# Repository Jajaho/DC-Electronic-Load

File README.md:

# DC-Electronic-Load
Digitally controlled dc electronic load.  

To cut costs, the core idea is to use multiple smaller low-cost MOSFETs in parallel instead of a single higher-power device.
Since the current through a semiconductor has a positive temperature coefficient this presents a novel engineering challenge. An unsuitable design could risk a thermal runaway event where a single transistor would handle increasingly larger currents until failure. To prevent such a catastrophic event a circuit to ensure equal current distribution is implemented.  

The instrument should feature constant current, voltage and power modes. Over-voltage and current protection is also desired.

This project was initially started in Eagle ECAD on 28.05.2019 but was never implemented.

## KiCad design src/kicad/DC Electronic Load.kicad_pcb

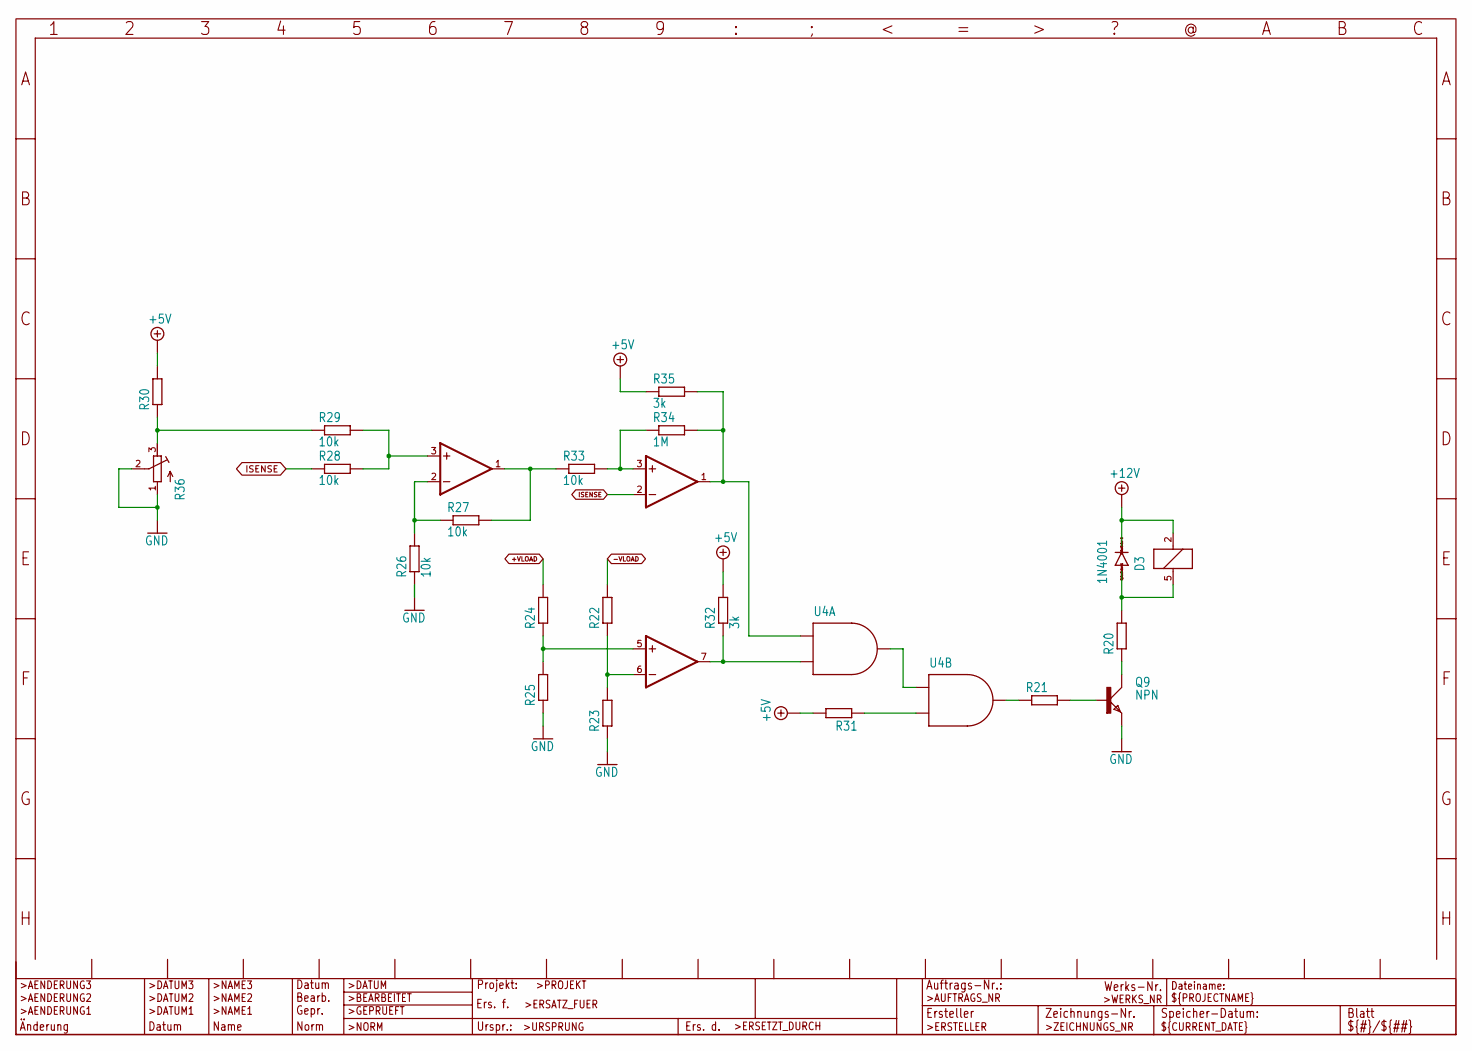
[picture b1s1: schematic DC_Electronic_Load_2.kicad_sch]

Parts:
D3: 1N4001; MELF-MLL41
IC1: LM393D; SO08
IC2: TL072D; SO08
K1: AZ8-FORM-C; AZ8
Q9: NPN; SOT23
R20, R21, R22, R23, R24, R25, R30, R31: R-EU_R1206; R1206
R26, R27, R28, R29, R33: 10k; R1206
R32, R35: 3k; R1206
R34: 1M; R1206
R36: R-TRIMM64W; RTRIM64W
U4: SN74AHC08; SOIC−14

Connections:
+5V: R30.2, R31.2, R32.2, R35.1; also elsewhere on the board
+12V: D3.C, K1.2 (1); also elsewhere on the board
+VLOAD: R24.2; also elsewhere on the board
-VLOAD: R22.2; also elsewhere on the board
GND: Q9.2 (E), R23.1, R25.1, R26.1, R36.1 (A), R36.2 (S); also elsewhere on the board
ISENSE: IC1.2 (-IN), R28.1; also elsewhere on the board
unnamed: IC1.6 (-IN), R22.1, R23.2
unnamed: IC1.5 (+IN), R24.1, R25.2
unnamed: IC1.7 (OUT), R32.1, U4.2 (B)
unnamed: D3.A, K1.5 (2), R20.2
unnamed: Q9.3 (C), R20.1
unnamed: U4.3 (Y), U4.4 (A)
unnamed: Q9.1 (B), R21.2
unnamed: R31.1, U4.5 (B)
unnamed: IC1.1 (OUT), R34.2, R35.2, U4.1 (A)
unnamed: IC2.3 (+IN), R28.2, R29.2
unnamed: IC2.2 (-IN), R26.2, R27.1
unnamed: IC2.1 (OUT), R27.2, R33.1
unnamed: IC1.3 (+IN), R33.2, R34.1
unnamed: R29.1, R30.1, R36.3 (E)
unnamed: R21.1, U4.6 (Y)

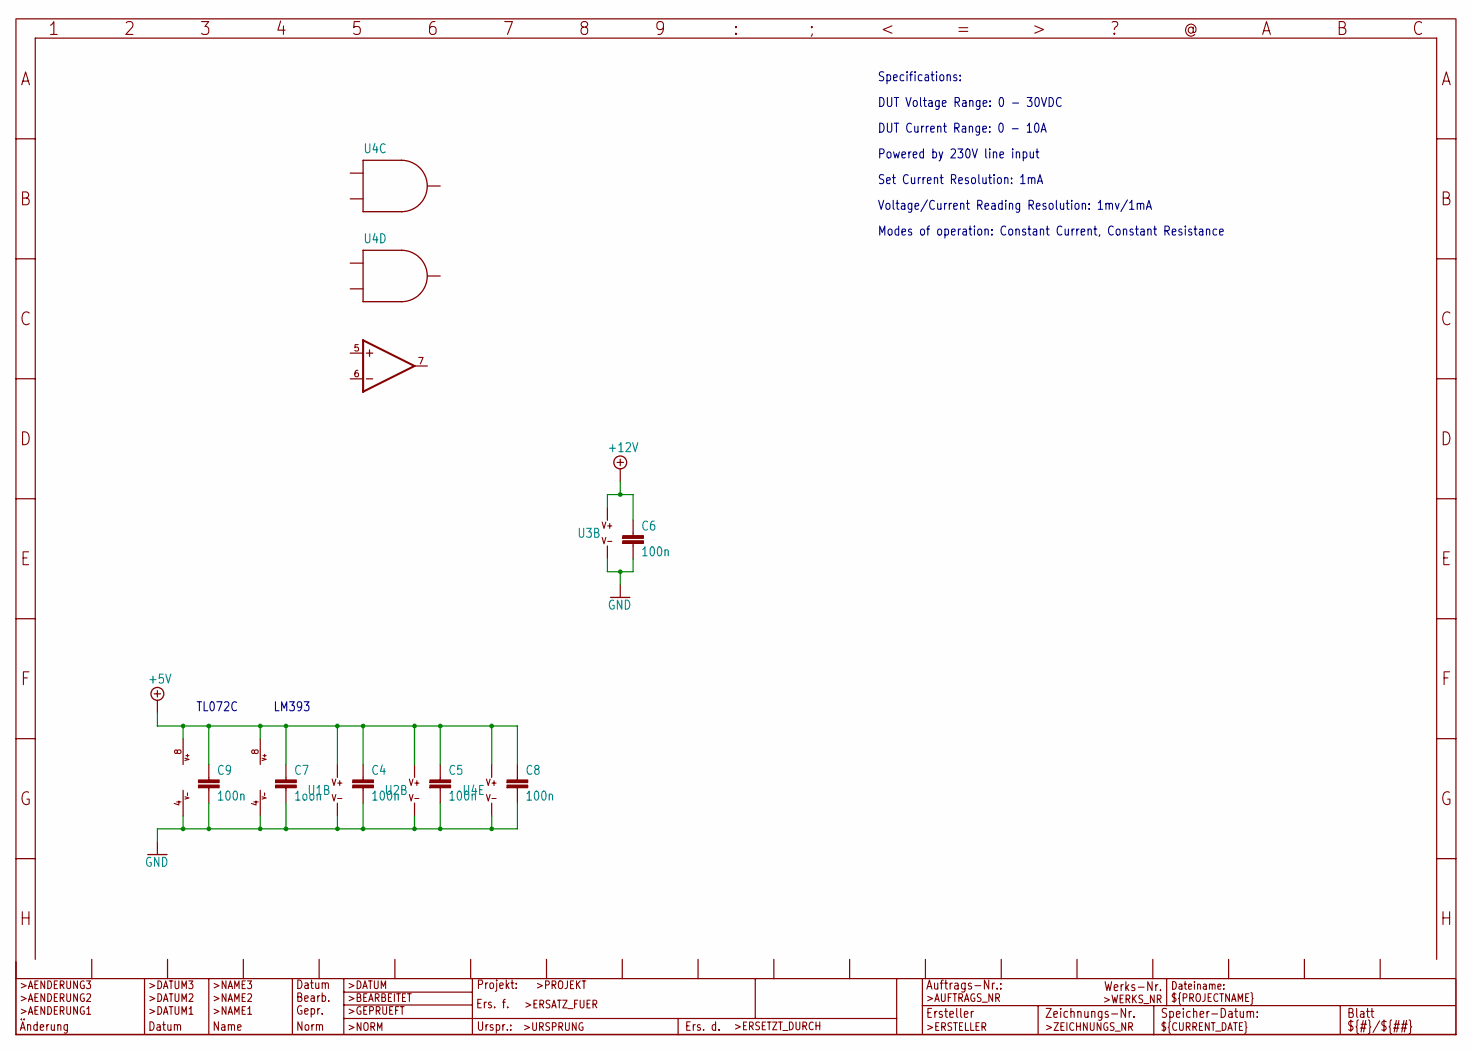
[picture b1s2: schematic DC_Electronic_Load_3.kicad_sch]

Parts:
C4, C5, C6, C8, C9: 100n; C1206
C7: 1oon; C1206
IC1: LM393D; SO08
IC2: TL072D; SO08
U1, U2, U3: AD8628; SOIC-8
U4: SN74AHC08; SOIC−14

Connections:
+5V: C4.1, C5.1, C7.1, C8.1, C9.1, IC1.8 (V+), IC2.8 (V+), U1.7 (V+), U2.7 (V+), U4.14 (V+); also elsewhere on the board
+12V: C6.1, U3.7 (V+); also elsewhere on the board
GND: C4.2, C5.2, C6.2, C7.2, C8.2, C9.2, IC1.4 (V-), IC2.4 (V-), U1.4 (V-), U2.4 (V-), U3.4 (V-), U4.7 (V-); also elsewhere on the board

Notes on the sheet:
Powered by 230V line input
Specifications:
DUT Voltage Range: 0 - 30VDC
Voltage/Current Reading Resolution: 1mv/1mA
DUT Current Range: 0 - 10A
LM393
Modes of operation: Constant Current, Constant Resistance
Set Current Resolution: 1mA
TL072C

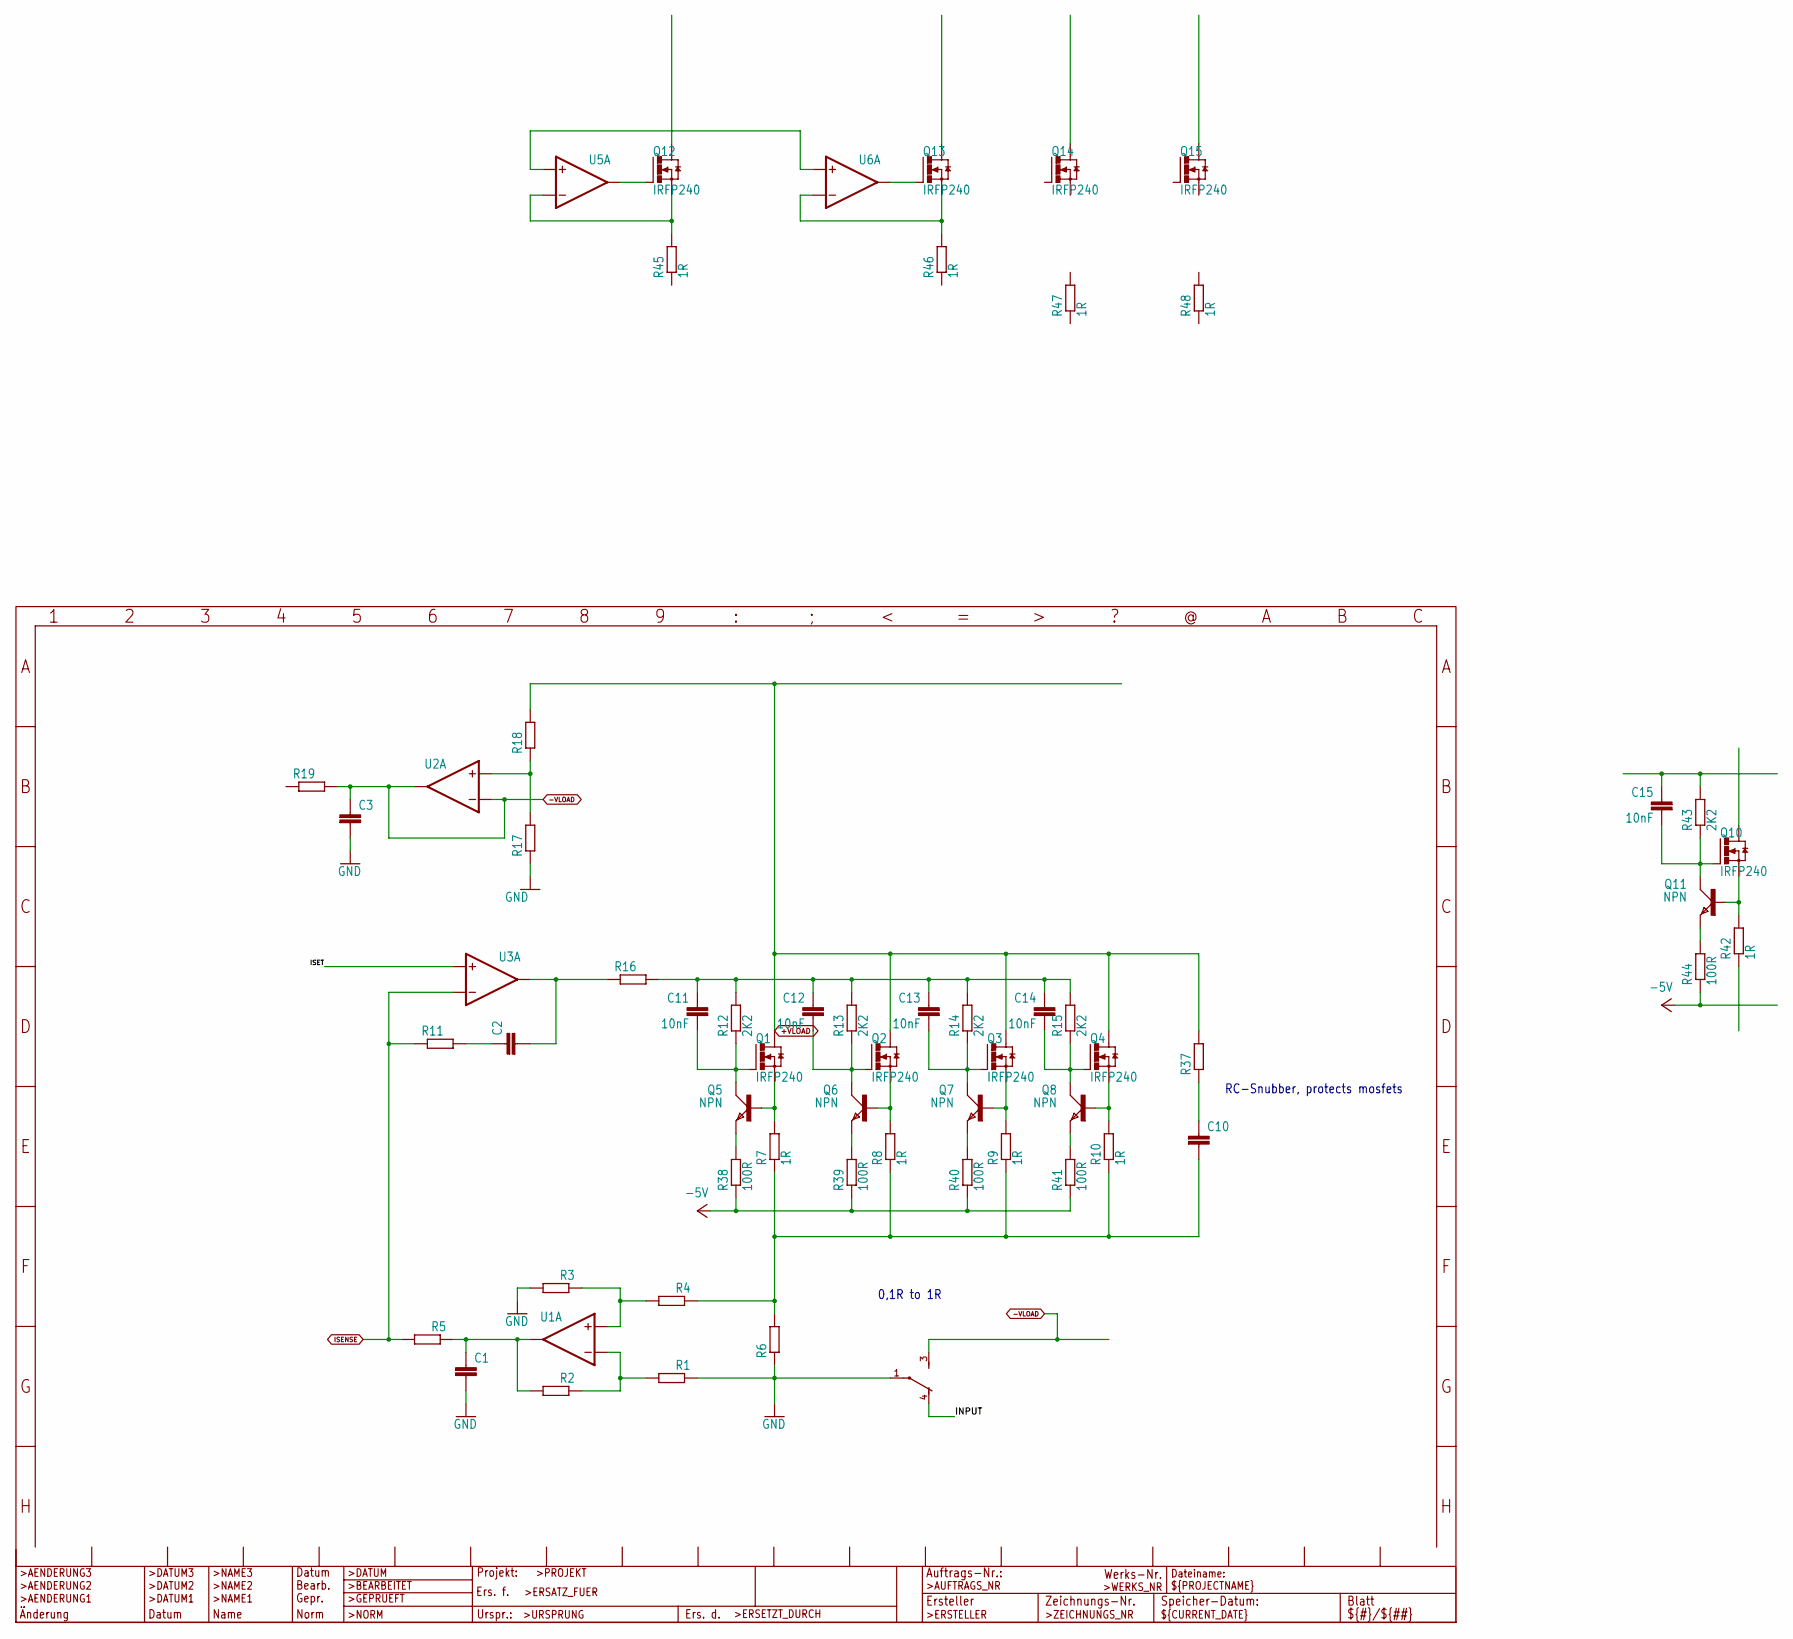
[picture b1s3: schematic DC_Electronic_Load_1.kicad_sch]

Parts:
C1, C2, C3, C10: C-EUC1206; C1206
C11, C12, C13, C14, C15: 10nF; C1206
K1: AZ8-FORM-C; AZ8
Q1, Q2, Q3, Q4, Q10, Q12, Q13, Q14, Q15: IRFP240; TO247BV
Q5, Q6, Q7, Q8, Q11: NPN; SOT23
R1, R2, R3, R4, R5, R6, R11, R16, R17, R18, R19, R37: R-EU_R1206; R1206
R7, R8, R9, R10, R42, R45, R46, R47, R48: 1R; VTA53
R12, R13, R14, R15, R43: 2K2; R1206
R38, R39, R40, R41, R44: 100R; R1206
U1, U2, U3, U5, U6: AD8628; SOIC-8

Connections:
+VLOAD: Q1.D, Q2.D, Q3.D, Q4.D, R18.2, R37.2; also elsewhere on the board
+VLOAD1: Q10.D
-5V: R38.1, R39.1, R40.1, R41.1, R44.1
-VLOAD: C3.1, K1.3 (S), R19.2, U2.2 (IN-), U2.6 (OUT); also elsewhere on the board
GND: C1.2, C3.2, K1.1, R1.1, R3.2, R6.1, R17.1; also elsewhere on the board
INPUT: K1.4 (O)
ISENSE: R5.2, R11.1, U3.2 (IN-); also elsewhere on the board
ISET: U3.3 (IN+)
unnamed: C1.1, R2.2, R5.1, U1.6 (OUT)
unnamed: R1.2, R2.1, U1.2 (IN-)
unnamed: R3.1, R4.2, U1.3 (IN+)
unnamed: C10.2, R4.1, R6.2, R7.1, R8.1, R9.1, R10.1
unnamed: C2.1, R11.2
unnamed: C2.2, R16.1, U3.6 (OUT)
unnamed: Q1.S, Q5.1 (B), R7.2
unnamed: Q2.S, Q6.1 (B), R8.2
unnamed: Q3.S, Q7.1 (B), R9.2
unnamed: Q4.S, Q8.1 (B), R10.2
unnamed: C11.1, C12.1, C13.1, C14.1, R12.2, R13.2, R14.2, R15.2, R16.2
unnamed: C11.2, Q1.G, Q5.3 (C), R12.1
unnamed: C12.2, Q2.G, Q6.3 (C), R13.1
unnamed: C13.2, Q3.G, Q7.3 (C), R14.1
unnamed: C14.2, Q4.G, Q8.3 (C), R15.1
unnamed: Q6.2 (E), R39.2
unnamed: R17.2, R18.1, U2.3 (IN+)
unnamed: C10.1, R37.1
unnamed: Q7.2 (E), R40.2
unnamed: Q8.2 (E), R41.2
unnamed: Q5.2 (E), R38.2
unnamed: Q10.S, Q11.1 (B), R42.2
unnamed: C15.1, R43.2
unnamed: C15.2, Q10.G, Q11.3 (C), R43.1
unnamed: Q11.2 (E), R44.2
unnamed: Q12.G, U5.6 (OUT)
unnamed: Q12.S, R45.2, U5.2 (IN-)
unnamed: Q13.S, R46.2, U6.2 (IN-)
unnamed: Q13.G, U6.6 (OUT)
unnamed: U5.3 (IN+), U6.3 (IN+)

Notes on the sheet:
0,1R to 1R
RC-Snubber, protects mosfets

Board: 2 copper layers, 88 parts (0 on the bottom side), 52 nets, no tracks yet.

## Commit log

2023-07-06 Add eagle project files
2023-07-13 Add kicad project imported from eagle
2023-07-13 Tidy up kicad schematic
